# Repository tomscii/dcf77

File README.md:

# Moved permanently

This repository has moved permanently,
because I am [ditching GitHub](https://tomscii.sig7.se/2024/01/Ditching-GitHub).

The new location of this code is
<https://git.hq.sig7.se/dcf77.git>.

If you wish to contribute or interact with it, please refer to
<https://git.hq.sig7.se> for general instructions.

## Give up GitHub!

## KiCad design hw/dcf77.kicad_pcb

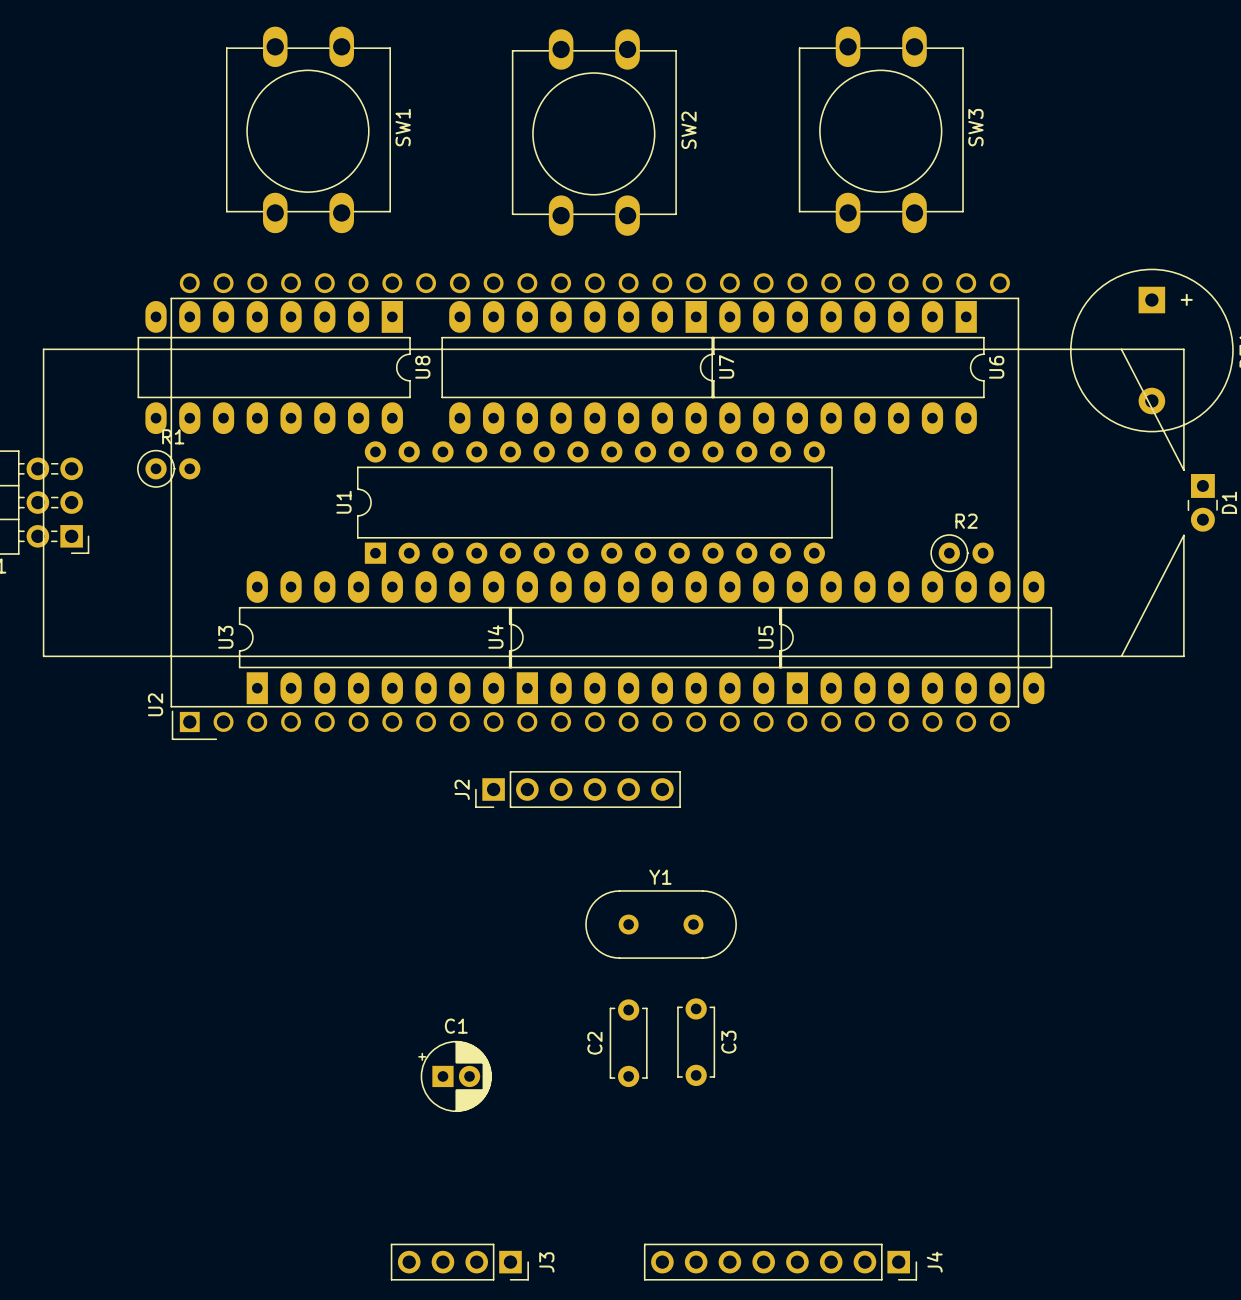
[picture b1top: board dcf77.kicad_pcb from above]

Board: 2 copper layers, 23 parts (0 on the bottom side), 76 nets, no tracks yet.

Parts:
BZ1: Buzzer; Buzzer_12x9.5RM7.6
C1: 47u; CP_Radial_D5.0mm_P2.00mm
C2, C3: 22p; C_Disc_D5.0mm_W2.5mm_P5.00mm
D1: LCD Backlight; LED_backlight_COM0621
J1: AVR-ISP-6; PinHeader_2x03_P2.54mm_Horizontal
J2: FTDI; PinHeader_1x06_P2.54mm_Vertical
J3: DHT22_Sensor; PinSocket_1x04_P2.54mm_Vertical
J4: DCF77_Decoder; PinSocket_1x08_P2.54mm_Vertical
R1: 10k; R_Axial_DIN0207_L6.3mm_D2.5mm_P2.54mm_Vertical
R2: 150; R_Axial_DIN0207_L6.3mm_D2.5mm_P2.54mm_Vertical
SW1: MODE; SW_PUSH-12mm
SW2: SET; SW_PUSH-12mm
SW3: ADJ; SW_PUSH-12mm
U1: ATmega328P-PU; DIP-28_W7.62mm
U2: DE122-XX-XX
U3, U4, U5, U6, U7, U8: 74HC595; DIP-16_W7.62mm_LongPads
Y1: 2MHz; Crystal_HC49-U_Vertical

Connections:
/ADJ: SW3.1, U1.15
/DCF77_POWER: J4.5, U1.13
/DCF77_S-: J4.1, U1.14
/DHT22_DATA: J3.2, U1.4
/DHT22_POWER: J3.1, U1.6
/LCD_CLK: U1.26, U3.11, U3.12, U4.11, U4.12, U5.11, U5.12, U6.11, U6.12, U7.11, U7.12, U8.11, U8.12
/LCD_COM: U1.27, U2.1
/LCD_DATA0: U1.23, U3.14
/LCD_DATA1: U1.24, U5.14
/LCD_DATA2: U1.25, U7.14
/LCD_OE-: U1.28, U3.13, U4.13, U5.13, U6.13, U7.13, U8.13
/MISO: J1.1, SW1.1, U1.18
/MOSI: J1.4, U1.17
/RST-: J1.5, R1.2, U1.1
/RxD: J2.4, U1.2
/SCK: J1.3, U1.19
/SEG_1A: U2.48, U8.5
/SEG_1B: U2.47, U8.4
/SEG_1C: U2.4, U3.2
/SEG_1D: U2.3, U3.1
/SEG_1DP: U2.5, U3.3
/SEG_1E: U2.2, U3.15
/SEG_1F: U2.49, U8.6
/SEG_1G: U2.50, U8.7
/SEG_2A: U2.44, U8.1
/SEG_2B: U2.43, U8.15
/SEG_2C: U2.8, U3.6
/SEG_2D: U2.7, U3.5
/SEG_2DP: U2.9, U3.7
/SEG_2E: U2.6, U3.4
/SEG_2F: U2.45, U8.2
/SEG_2G: U2.46, U8.3
/SEG_3A: U2.39, U7.5
/SEG_3B: U2.38, U7.4
/SEG_3C: U2.12, U4.2
/SEG_3D: U2.11, U4.1
/SEG_3DP: U2.13, U4.3
/SEG_3E: U2.10, U4.15
/SEG_3F: U2.40, U7.6
/SEG_3G: U2.41, U7.7
/SEG_4A: U2.35, U7.1
/SEG_4B: U2.34, U7.15
/SEG_4C: U2.16, U4.6
/SEG_4D: U2.15, U4.5
/SEG_4DP: U2.17, U4.7
/SEG_4E: U2.14, U4.4
/SEG_4F: U2.36, U7.2
/SEG_4G: U2.37, U7.3
/SEG_5A: U2.30, U6.4
/SEG_5B: U2.29, U6.3
/SEG_5C: U2.20, U5.2
/SEG_5D: U2.19, U5.1
/SEG_5DP: U2.21, U5.3
/SEG_5E: U2.18, U5.15
/SEG_5F: U2.31, U6.5
/SEG_5G: U2.32, U6.6
/SEG_6A: U2.26, U6.15
/SEG_6B: U2.25, U5.7
/SEG_6C: U2.24, U5.6
/SEG_6D: U2.23, U5.5
/SEG_6E: U2.22, U5.4
/SEG_6F: U2.27, U6.1
/SEG_6G: U2.28, U6.2
/SEG_COL: U2.33, U2.42, U6.7
/SET: SW2.1, U1.16
/TxD: J2.5, U1.3
GND: BZ1.2, C1.2, C2.1, C3.2, D1.1, J1.6, J2.1, J2.2, J3.3, J3.4, J4.7, SW1.2, SW2.2, SW3.2, U1.8, U1.22, U3.8, U4.8, U5.8, U6.8, U7.8, U8.8
unnamed: BZ1.1, U1.12
unnamed: C2.2, U1.9, Y1.1
unnamed: C3.1, U1.10, Y1.2
unnamed: D1.2, R2.1
unnamed: R2.2, U1.5
unnamed: U3.9, U4.14
unnamed: U5.9, U6.14
unnamed: U7.9, U8.14
VCC: C1.1, J1.2, J2.3, R1.1, U1.7, U1.20, U1.21, U3.10, U3.16, U4.10, U4.16, U5.10, U5.16, U6.10, U6.16, U7.10, U7.16, U8.10, U8.16

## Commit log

2021-09-21 PWM and LCD control PoC
2021-09-21 Module breakout
2021-09-22 LCD driver
2021-09-23 LED driver interface via PWM
2021-09-23 Add datasheet for 5mm RGB common-cathode LED
2021-09-25 PWM module: support piezo on/off, etc.
2021-09-27 Clock rate adjustment to fine-tune (correct) crystal frequency
2021-09-30 DHT22 sensor interface; double MCU clock and USART baudrate
2021-09-30 Add user interface description / plan
2021-10-01 DCF77 receiver interface base
2021-10-08 Adjust hardware plan to built prototype; LCD display driver
2021-10-18 DCF77: basic synchronization
2021-10-22 DCF77 sync schedule and persistent local clock adjustment
2021-10-22 Improved DCF77 sync (no dropout in LCD updates)
2021-10-23 Avoid bleeding current through internal pull-ups
    This lowers the current consumption, when DCF77 and DHT22 modules are
    off, from ~170 uA to ~67 uA.
2021-10-25 Signed-math corrections to DCF77 clock synchronizer
2021-10-29 DCF77 improvements
    - sync in one minute instead of two
    - sync every 3AM and look out for DST changes
    - code cleanup: use char instead of int8_t (and uint8_t in some places)
    - LCD: no zero padding for hour
2021-10-30 Refactor LCD display driver for better performance
    - remove the intermediary storage of 3 16-bit integers
    - remove the commit phase
    - on-the-fly invert LCD_DATA bits for the negative frame
    (this makes timing asymmetrical, but only very slightly)
2021-11-01 Time- and date-keeping enhancements
2021-11-03 Add simavr-based simulator
2021-11-04 Add button events and some display screens; improve sync schedule
2021-11-24 Temperature & humidity sensor scheduler and display screen
2021-12-29 More robust sensor readout
    - the sensor is read out twice after power-on, because on the first
    readout, it might still return an old value from a previous
    measurement made a long time ago, and this way the value would
    never change if the sensor was powered on for a single readout
    every now and then.
    if readouts are performed with a period that fits into the
2022-01-08 Protect against bogus date received
2022-01-26 Backlight control
    We only have a monochrome (white) backlight module behind the LCD.
    The RED pwm-channel is used to drive the single backlight LED.
2022-03-23 Refined button event lifecycle, allow cycling screens by holding MODE
2022-06-10 Add KiCAD files for hardware design
    This is more for documentation than design purposes,
    as the device is already functional (as a handmade prototype).
2022-06-10 Improve simulator README
2022-06-18 Add PCB footprint for LCD backlight
2022-11-04 Updates before publication
2024-01-10 Migration notice
